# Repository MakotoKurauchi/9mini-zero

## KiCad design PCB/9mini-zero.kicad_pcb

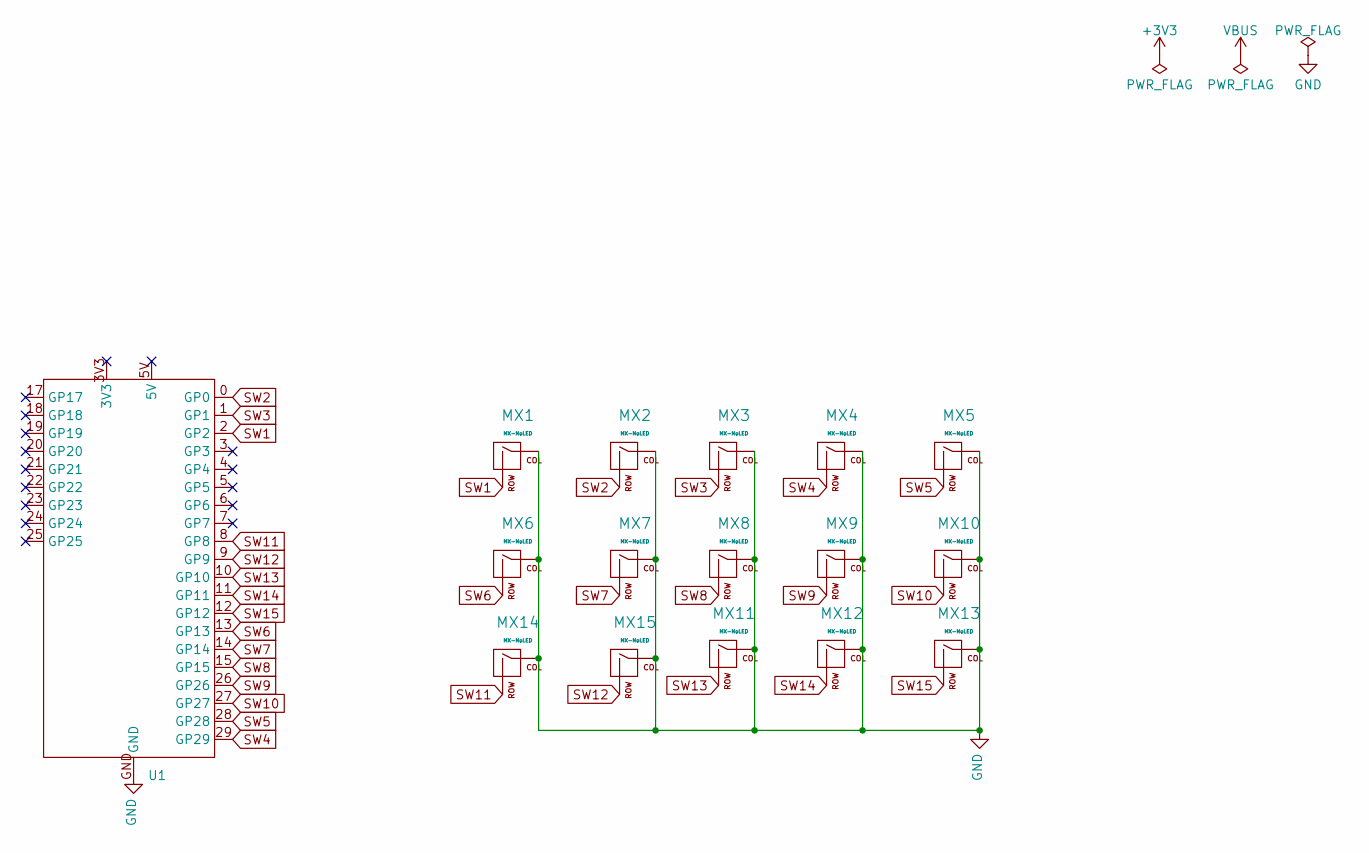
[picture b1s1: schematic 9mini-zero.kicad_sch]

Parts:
MX1, MX2, MX3, MX4, MX7, MX8, MX9, MX12, MX13, MX14, MX15: MX-NoLED; MXOnly-1U-NoLED
MX5, MX11: MX-NoLED; MXOnly-2U-NoLED
MX6, MX10: MX-NoLED; MXOnly-1.5U-NoLED
U1: Waveshare RP2040-Zero-TH

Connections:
GND: MX1.1 (COL), MX2.1 (COL), MX3.1 (COL), MX4.1 (COL), MX5.1 (COL), MX6.1 (COL), MX7.1 (COL), MX8.1 (COL), MX9.1 (COL), MX10.1 (COL), MX11.1 (COL), MX12.1 (COL), MX13.1 (COL), MX14.1 (COL), MX15.1 (COL), U1.GND
SW1: MX1.2 (ROW), U1.2 (GP2)
SW2: MX2.2 (ROW), U1.0 (GP0)
SW3: MX3.2 (ROW), U1.1 (GP1)
SW4: MX4.2 (ROW), U1.29 (GP29)
SW5: MX5.2 (ROW), U1.28 (GP28)
SW6: MX6.2 (ROW), U1.13 (GP13)
SW7: MX7.2 (ROW), U1.14 (GP14)
SW8: MX8.2 (ROW), U1.15 (GP15)
SW9: MX9.2 (ROW), U1.26 (GP26)
SW10: MX10.2 (ROW), U1.27 (GP27)
SW11: MX14.2 (ROW), U1.8 (GP8)
SW12: MX15.2 (ROW), U1.9 (GP9)
SW13: MX11.2 (ROW), U1.10 (GP10)
SW14: MX12.2 (ROW), U1.11 (GP11)
SW15: MX13.2 (ROW), U1.12 (GP12)

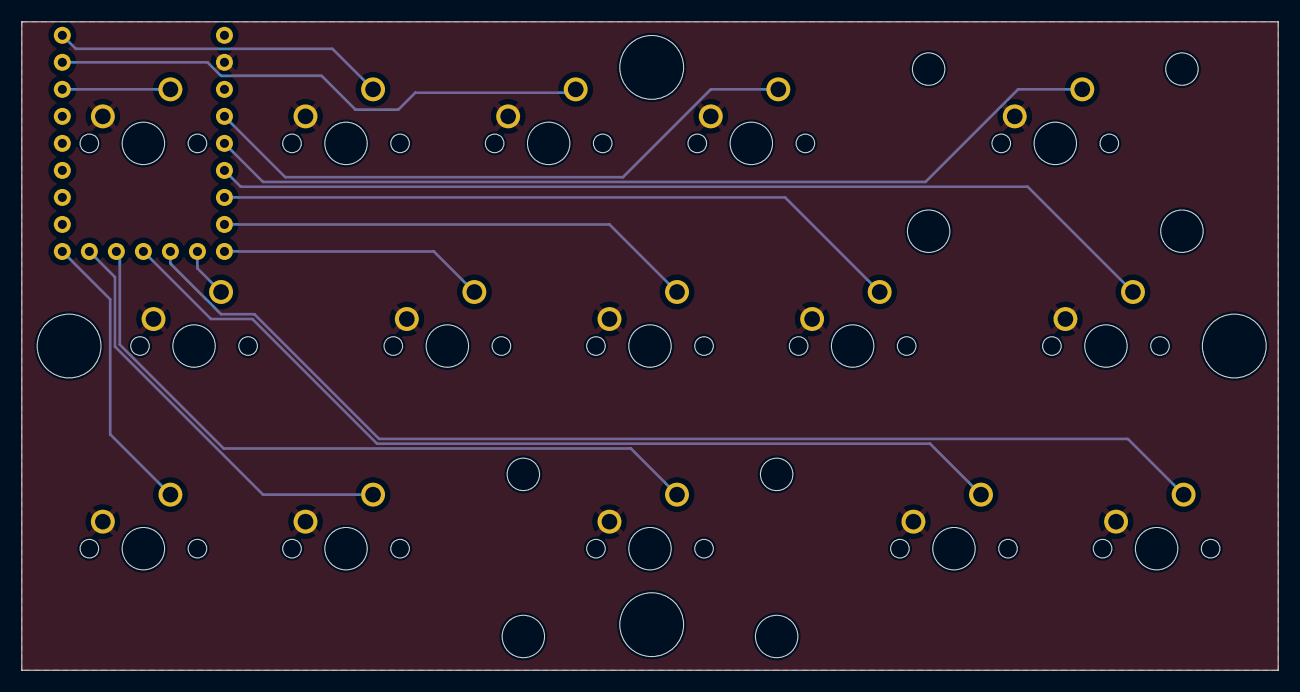
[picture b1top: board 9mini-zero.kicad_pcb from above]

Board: 2 copper layers, 118.1 x 61.0 mm, 16 parts (1 on the bottom side), 16 nets.

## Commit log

2023-04-26 layout
2023-04-27 board layout
